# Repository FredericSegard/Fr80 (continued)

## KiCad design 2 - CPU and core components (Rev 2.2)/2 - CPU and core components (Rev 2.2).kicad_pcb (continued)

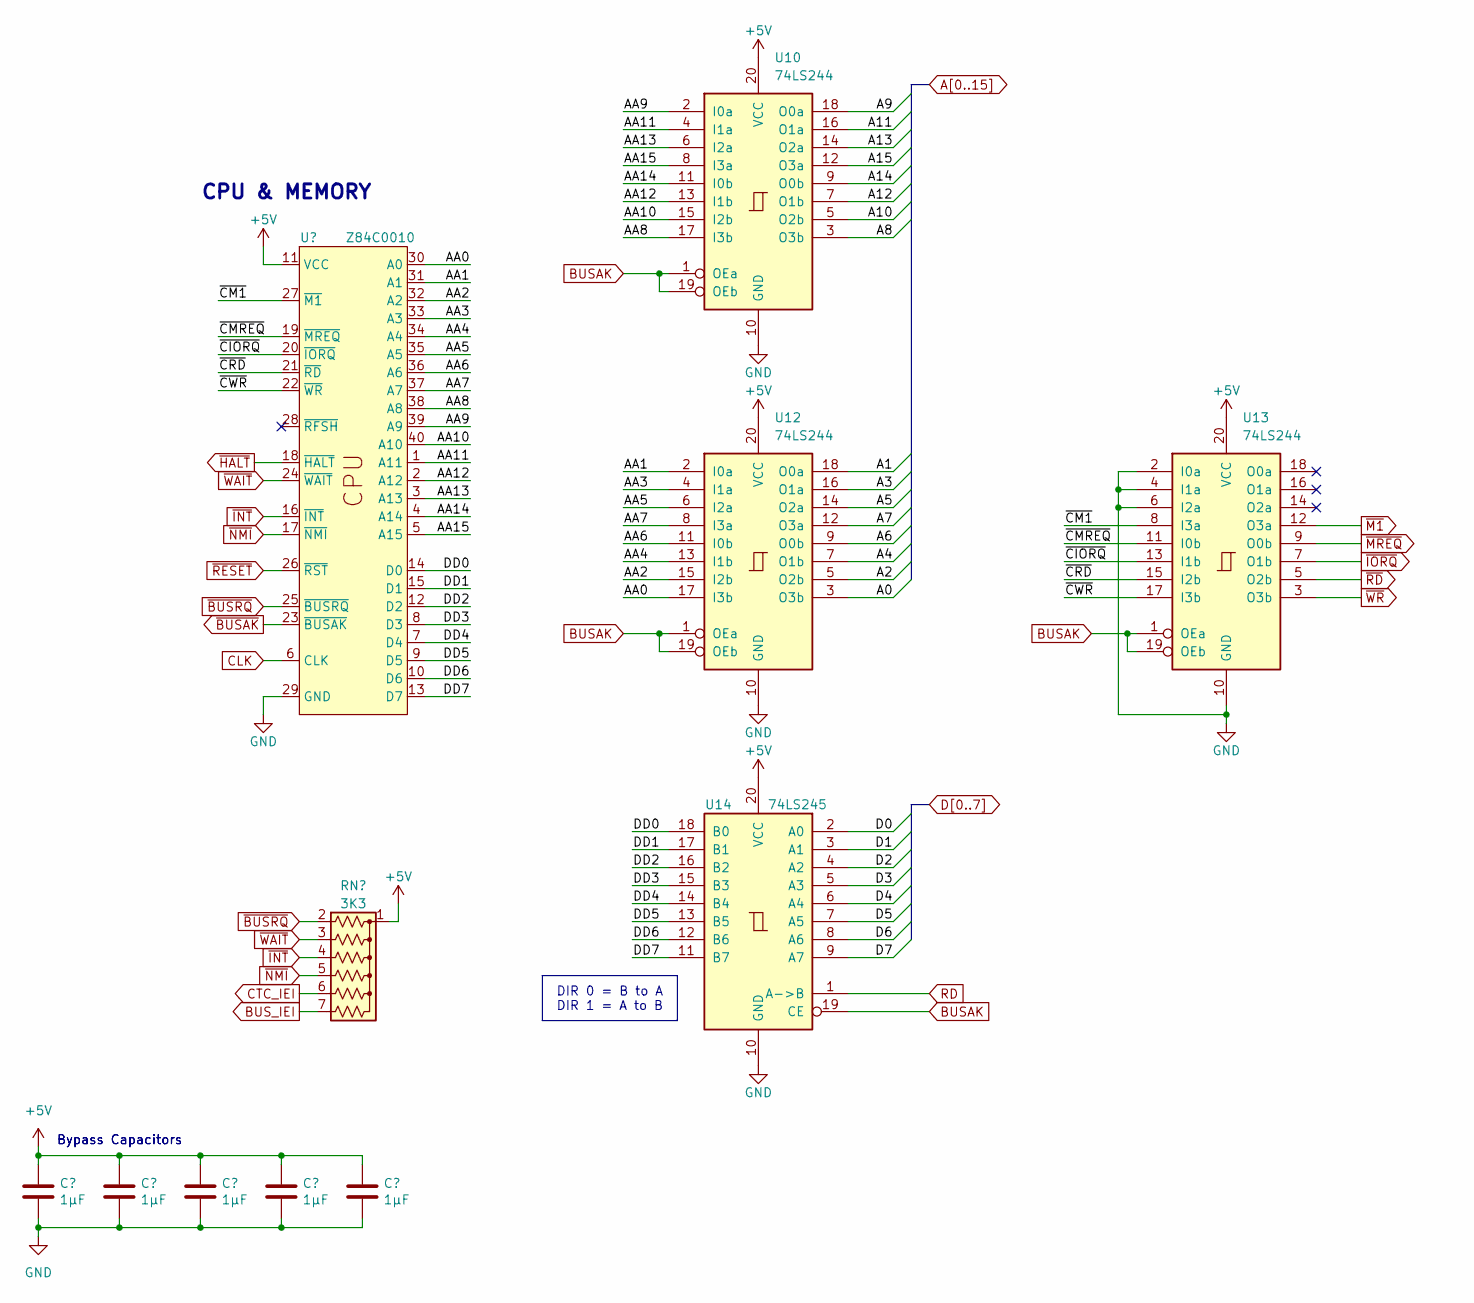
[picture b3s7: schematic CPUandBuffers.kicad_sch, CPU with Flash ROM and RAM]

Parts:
C12, C13, C14, C15, C16: 1µF; C_Disc_D3.4mm_W2.1mm_P2.50mm
RN4: 3K3; R_Array_SIP7
U10, U12, U13: 74LS244; DIP-20_W7.62mm_Socket
U11: Z84C0010; DIP-40_W15.24mm_Socket
U14: 74LS245; DIP-20_W7.62mm_Socket

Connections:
+5V: C12.1, C13.1, C14.1, C15.1, C16.1, RN4.1 (common), U10.20 (VCC), U11.11 (VCC), U12.20 (VCC), U13.20 (VCC), U14.20 (VCC); also elsewhere on the board
/CPU and Buffers/AA0: U11.30 (A0), U12.17 (I3b)
/CPU and Buffers/AA1: U11.31 (A1), U12.2 (I0a)
/CPU and Buffers/AA2: U11.32 (A2), U12.15 (I2b)
/CPU and Buffers/AA3: U11.33 (A3), U12.4 (I1a)
/CPU and Buffers/AA4: U11.34 (A4), U12.13 (I1b)
/CPU and Buffers/AA5: U11.35 (A5), U12.6 (I2a)
/CPU and Buffers/AA6: U11.36 (A6), U12.11 (I0b)
/CPU and Buffers/AA7: U11.37 (A7), U12.8 (I3a)
/CPU and Buffers/AA8: U10.17 (I3b), U11.38 (A8)
/CPU and Buffers/AA9: U10.2 (I0a), U11.39 (A9)
/CPU and Buffers/AA10: U10.15 (I2b), U11.40 (A10)
/CPU and Buffers/AA11: U10.4 (I1a), U11.1 (A11)
/CPU and Buffers/AA12: U10.13 (I1b), U11.2 (A12)
/CPU and Buffers/AA13: U10.6 (I2a), U11.3 (A13)
/CPU and Buffers/AA14: U10.11 (I0b), U11.4 (A14)
/CPU and Buffers/AA15: U10.8 (I3a), U11.5 (A15)
/CPU and Buffers/DD0: U11.14 (D0), U14.18 (B0)
/CPU and Buffers/DD1: U11.15 (D1), U14.17 (B1)
/CPU and Buffers/DD2: U11.12 (D2), U14.16 (B2)
/CPU and Buffers/DD3: U11.8 (D3), U14.15 (B3)
/CPU and Buffers/DD4: U11.7 (D4), U14.14 (B4)
/CPU and Buffers/DD5: U11.9 (D5), U14.13 (B5)
/CPU and Buffers/DD6: U11.10 (D6), U14.12 (B6)
/CPU and Buffers/DD7: U11.13 (D7), U14.11 (B7)
/CPU and Buffers/~CIORQ: U11.20 (~IORQ), U13.13 (I1b)
/CPU and Buffers/~CM1: U11.27 (~M1), U13.8 (I3a)
/CPU and Buffers/~CMREQ: U11.19 (~MREQ), U13.11 (I0b)
/CPU and Buffers/~CRD: U11.21 (~RD), U13.15 (I2b)
/CPU and Buffers/~CWR: U11.22 (~WR), U13.17 (I3b)
A0: U12.3 (O3b); also elsewhere on the board
A1: U12.18 (O0a); also elsewhere on the board
A2: U12.5 (O2b); also elsewhere on the board
A3: U12.16 (O1a); also elsewhere on the board
A4: U12.7 (O1b); also elsewhere on the board
A5: U12.14 (O2a); also elsewhere on the board
A6: U12.9 (O0b); also elsewhere on the board
A7: U12.12 (O3a); also elsewhere on the board
A8: U10.3 (O3b); also elsewhere on the board
A9: U10.18 (O0a); also elsewhere on the board
A10: U10.5 (O2b); also elsewhere on the board
A11: U10.16 (O1a); also elsewhere on the board
A12: U10.7 (O1b); also elsewhere on the board
A13: U10.14 (O2a); also elsewhere on the board
A14: U10.9 (O0b); also elsewhere on the board
A15: U10.12 (O3a); also elsewhere on the board
BUSAK: U10.1 (OEa), U10.19 (OEb), U12.1 (OEa), U12.19 (OEb), U13.1 (OEa), U13.19 (OEb), U14.19 (CE); also elsewhere on the board
BUS_IEI: RN4.7 (R6); also elsewhere on the board
CLK: U11.6 (CLK); also elsewhere on the board
CTC_IEI: RN4.6 (R5); also elsewhere on the board
D0: U14.2 (A0); also elsewhere on the board
D1: U14.3 (A1); also elsewhere on the board
D2: U14.4 (A2); also elsewhere on the board
D3: U14.5 (A3); also elsewhere on the board
D4: U14.6 (A4); also elsewhere on the board
D5: U14.7 (A5); also elsewhere on the board
D6: U14.8 (A6); also elsewhere on the board
D7: U14.9 (A7); also elsewhere on the board
GND: C12.2, C13.2, C14.2, C15.2, C16.2, U10.10 (GND), U11.29 (GND), U12.10 (GND), U13.2 (I0a), U13.4 (I1a), U13.6 (I2a), U13.10 (GND), U14.10 (GND); also elsewhere on the board
RD: U14.1 (A->B); also elsewhere on the board
~BUSAK: U11.23 (~BUSAK); also elsewhere on the board
~BUSRQ: RN4.2 (R1), U11.25 (~BUSRQ); also elsewhere on the board
~HALT: U11.18 (~HALT); also elsewhere on the board
~INT: RN4.4 (R3), U11.16 (~INT); also elsewhere on the board
~IORQ: U13.7 (O1b); also elsewhere on the board
~M1: U13.12 (O3a); also elsewhere on the board
~MREQ: U13.9 (O0b); also elsewhere on the board
~NMI: RN4.5 (R4), U11.17 (~NMI); also elsewhere on the board
~RD: U13.5 (O2b); also elsewhere on the board
~RESET: U11.26 (~RST); also elsewhere on the board
~WAIT: RN4.3 (R2), U11.24 (~WAIT); also elsewhere on the board
~WR: U13.3 (O3b); also elsewhere on the board

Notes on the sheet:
DIR 0 = B to A DIR 1 = A to B
Bypass Capacitors
CPU & MEMORY

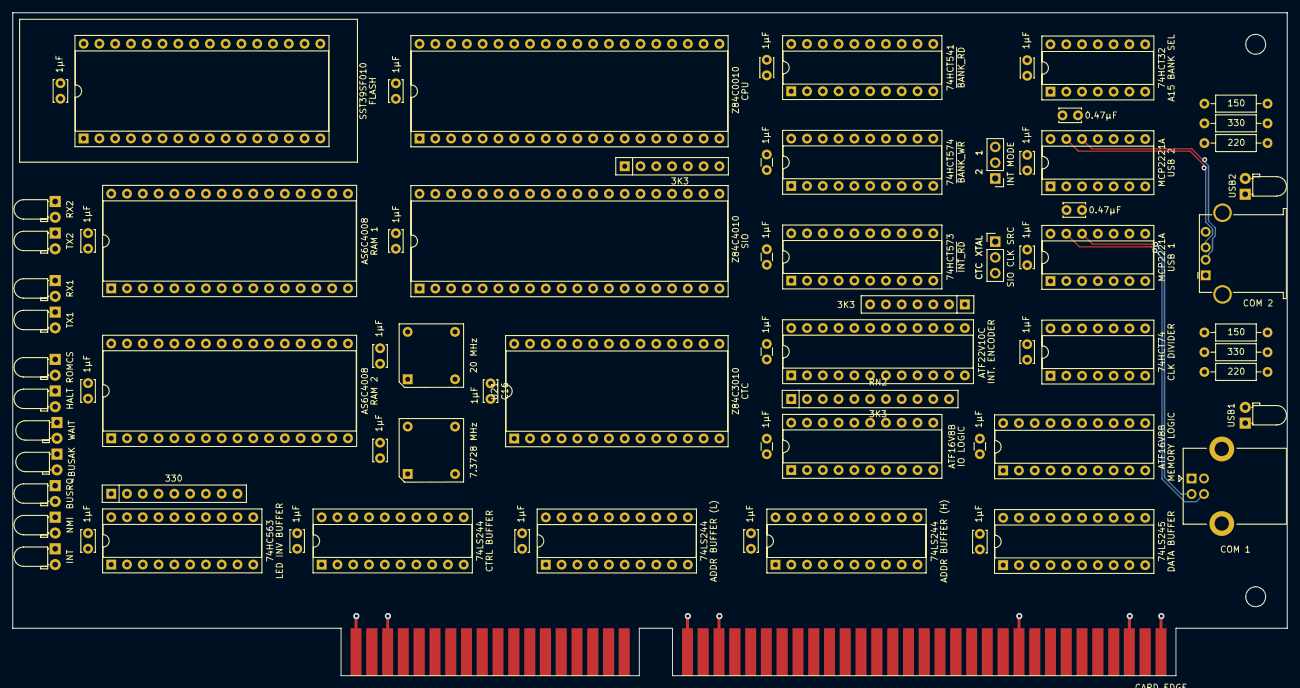
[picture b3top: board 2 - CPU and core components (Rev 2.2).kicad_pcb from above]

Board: 4 copper layers, 205.1 x 106.7 mm, 76 parts (0 on the bottom side), 160 nets.

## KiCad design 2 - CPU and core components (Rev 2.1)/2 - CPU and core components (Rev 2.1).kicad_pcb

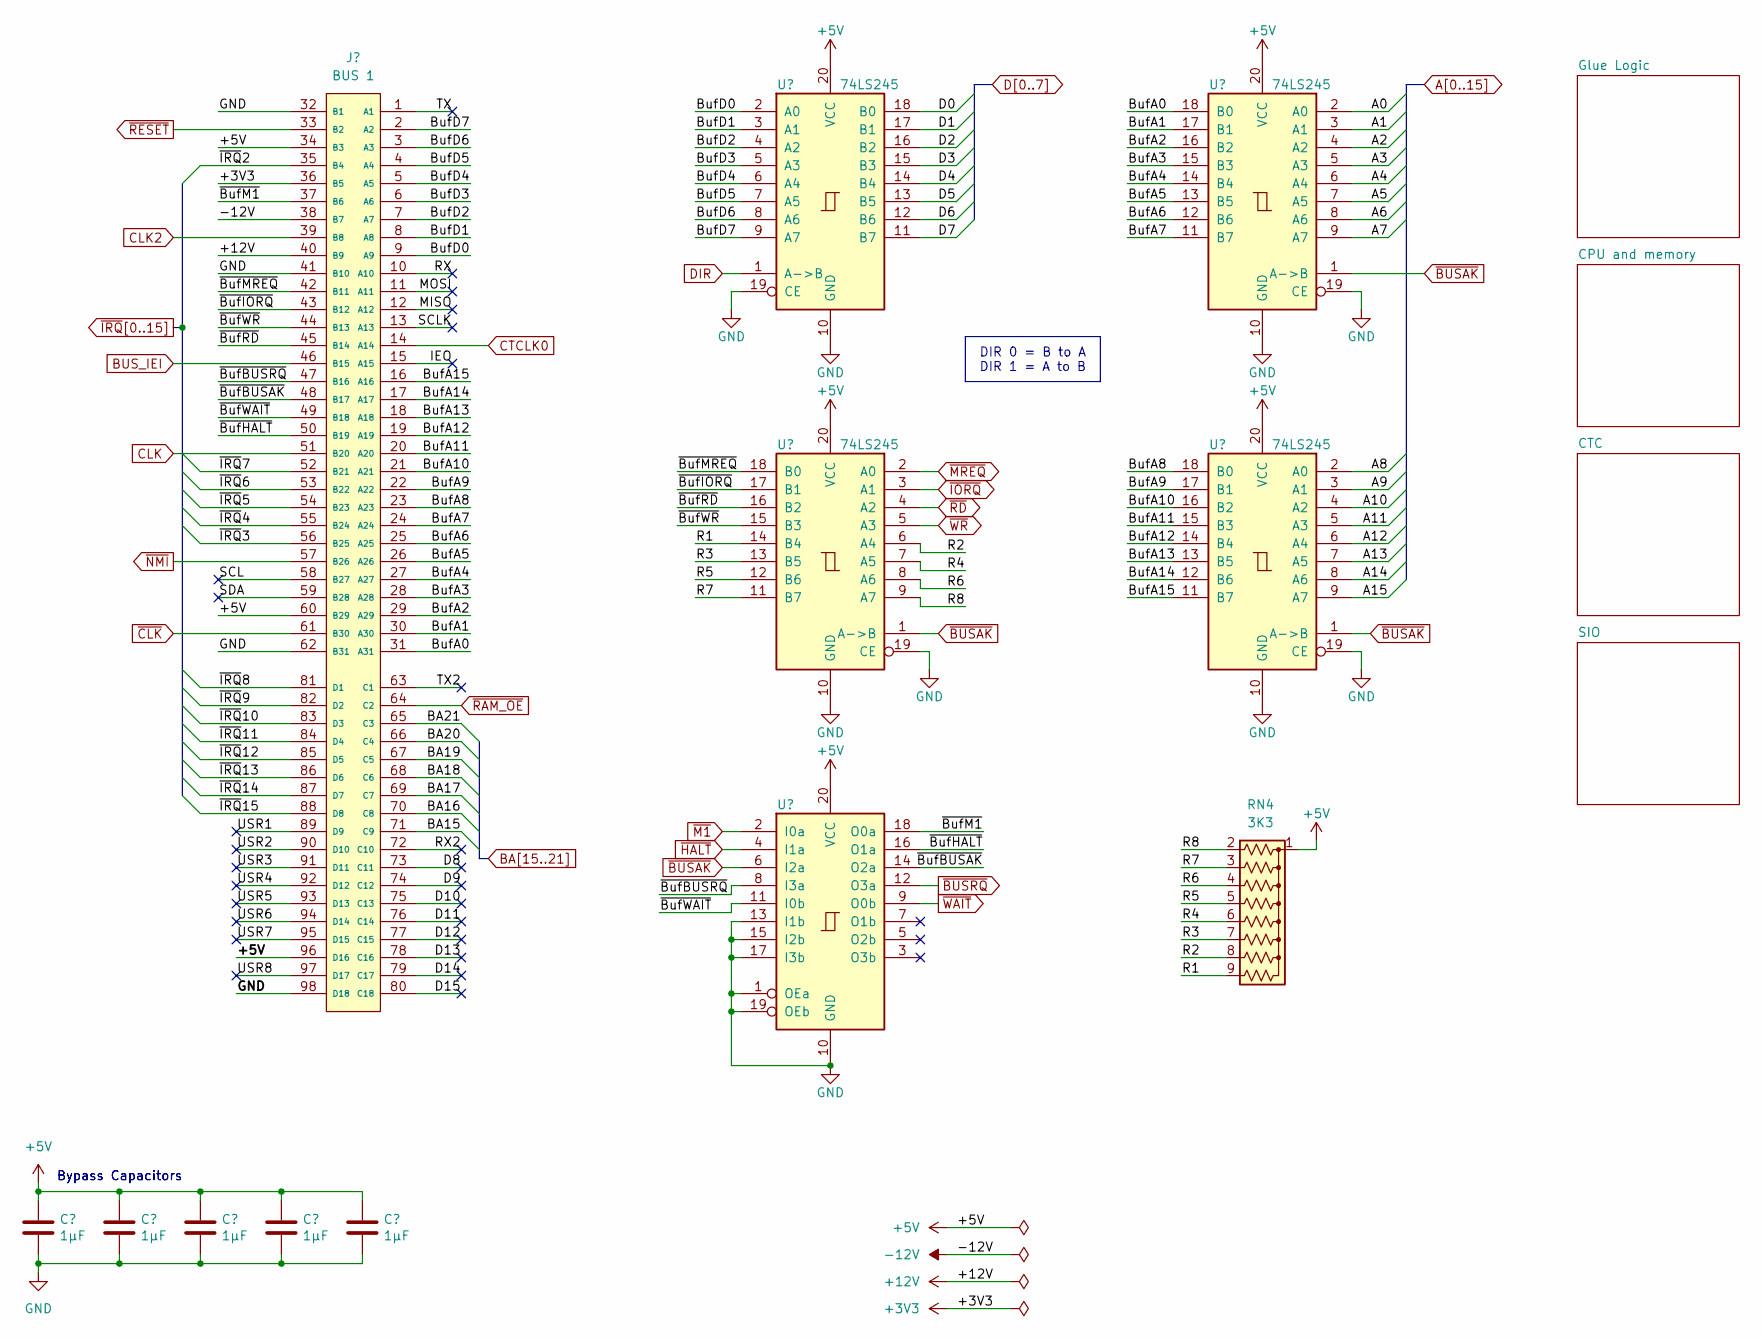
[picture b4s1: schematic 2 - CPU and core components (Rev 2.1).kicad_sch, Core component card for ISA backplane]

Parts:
C1, C2, C3, C4, C5: 1µF; C_Disc_D3.4mm_W2.1mm_P2.50mm
J1: BUS 1; BUS_AT v2
RN4: 3K3; R_Array_SIP9
U1, U2, U4, U5: 74LS245; DIP-20_W7.62mm_Socket
U3: 74LS244; DIP-20_W7.62mm_Socket

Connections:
+3V3: J1.36 (B5)
+12V: J1.40 (B9)
-12V: J1.38 (B7)
/BufA0: J1.31 (A31), U4.18 (B0)
/BufA1: J1.30 (A30), U4.17 (B1)
/BufA2: J1.29 (A29), U4.16 (B2)
/BufA3: J1.28 (A28), U4.15 (B3)
/BufA4: J1.27 (A27), U4.14 (B4)
/BufA5: J1.26 (A26), U4.13 (B5)
/BufA6: J1.25 (A25), U4.12 (B6)
/BufA7: J1.24 (A24), U4.11 (B7)
/BufA8: J1.23 (A23), U5.18 (B0)
/BufA9: J1.22 (A22), U5.17 (B1)
/BufA10: J1.21 (A21), U5.16 (B2)
/BufA11: J1.20 (A20), U5.15 (B3)
/BufA12: J1.19 (A19), U5.14 (B4)
/BufA13: J1.18 (A18), U5.13 (B5)
/BufA14: J1.17 (A17), U5.12 (B6)
/BufA15: J1.16 (A16), U5.11 (B7)
/BufD0: J1.9 (A9), U1.2 (A0)
/BufD1: J1.8 (A8), U1.3 (A1)
/BufD2: J1.7 (A7), U1.4 (A2)
/BufD3: J1.6 (A6), U1.5 (A3)
/BufD4: J1.5 (A5), U1.6 (A4)
/BufD5: J1.4 (A4), U1.7 (A5)
/BufD6: J1.3 (A3), U1.8 (A6)
/BufD7: J1.2 (A2), U1.9 (A7)
/D8: J1.73 (C11)
/D9: J1.74 (C12)
/D10: J1.75 (C13)
/D11: J1.76 (C14)
/D12: J1.77 (C15)
/D13: J1.78 (C16)
/D14: J1.79 (C17)
/D15: J1.80 (C18)
/IEO: J1.15 (A15)
/MISO: J1.12 (A12)
/MOSI: J1.11 (A11)
/R1: RN4.9 (R8), U2.14 (B4)
/R2: RN4.8 (R7), U2.6 (A4)
/R3: RN4.7 (R6), U2.13 (B5)
/R4: RN4.6 (R5), U2.7 (A5)
/R5: RN4.5 (R4), U2.12 (B6)
/R6: RN4.4 (R3), U2.8 (A6)
/R7: RN4.3 (R2), U2.11 (B7)
/R8: RN4.2 (R1), U2.9 (A7)
/RX: J1.10 (A10)
/RX2: J1.72 (C10)
/SCL: J1.58 (B27)
/SCLK: J1.13 (A13)
/SDA: J1.59 (B28)
/TX: J1.1 (A1)
/TX2: J1.63 (C1)
/USR1: J1.89 (D9)
/USR2: J1.90 (D10)
/USR3: J1.91 (D11)
/USR4: J1.92 (D12)
/USR5: J1.93 (D13)
/USR6: J1.94 (D14)
/USR7: J1.95 (D15)
/USR8: J1.97 (D17)
/~BufBUSAK: J1.48 (B17), U3.14 (O2a)
/~BufBUSRQ: J1.47 (B16), U3.8 (I3a)
/~BufHALT: J1.50 (B19), U3.16 (O1a)
/~BufIORQ: J1.43 (B12), U2.17 (B1)
/~BufM1: J1.37 (B6), U3.18 (O0a)
/~BufMREQ: J1.42 (B11), U2.18 (B0)
/~BufRD: J1.45 (B14), U2.16 (B2)
/~BufWAIT: J1.49 (B18), U3.11 (I0b)
/~BufWR: J1.44 (B13), U2.15 (B3)
A0: U4.2 (A0); also elsewhere on the board
A1: U4.3 (A1); also elsewhere on the board
A2: U4.4 (A2); also elsewhere on the board
A3: U4.5 (A3); also elsewhere on the board
A4: U4.6 (A4); also elsewhere on the board
A5: U4.7 (A5); also elsewhere on the board
A6: U4.8 (A6); also elsewhere on the board
A7: U4.9 (A7); also elsewhere on the board
A8: U5.2 (A0); also elsewhere on the board
A9: U5.3 (A1); also elsewhere on the board
A10: U5.4 (A2); also elsewhere on the board
A11: U5.5 (A3); also elsewhere on the board
A12: U5.6 (A4); also elsewhere on the board
A13: U5.7 (A5); also elsewhere on the board
A14: U5.8 (A6); also elsewhere on the board
A15: U5.9 (A7); also elsewhere on the board
BA15: J1.71 (C9); also elsewhere on the board
BA16: J1.70 (C8); also elsewhere on the board
BA17: J1.69 (C7); also elsewhere on the board
BA18: J1.68 (C6); also elsewhere on the board
BA19: J1.67 (C5); also elsewhere on the board
BA20: J1.66 (C4); also elsewhere on the board
BA21: J1.65 (C3); also elsewhere on the board
BUS_IEI: J1.46 (B15); also elsewhere on the board
CLK: J1.51 (B20); also elsewhere on the board
CLK2: J1.39 (B8); also elsewhere on the board
CTCLK0: J1.14 (A14); also elsewhere on the board
D0: U1.18 (B0); also elsewhere on the board
D1: U1.17 (B1); also elsewhere on the board
D2: U1.16 (B2); also elsewhere on the board
D3: U1.15 (B3); also elsewhere on the board
D4: U1.14 (B4); also elsewhere on the board
D5: U1.13 (B5); also elsewhere on the board
D6: U1.12 (B6); also elsewhere on the board
D7: U1.11 (B7); also elsewhere on the board
DIR: U1.1 (A->B); also elsewhere on the board
~BUSAK: U2.1 (A->B), U3.6 (I2a), U4.1 (A->B), U5.1 (A->B); also elsewhere on the board
~BUSRQ: U3.12 (O3a); also elsewhere on the board
~CLK: J1.61 (B30); also elsewhere on the board
~HALT: U3.4 (I1a); also elsewhere on the board
~IORQ: U2.3 (A1); also elsewhere on the board
~IRQ2: J1.35 (B4); also elsewhere on the board
~IRQ3: J1.56 (B25); also elsewhere on the board
~IRQ4: J1.55 (B24); also elsewhere on the board
~IRQ5: J1.54 (B23); also elsewhere on the board
~IRQ6: J1.53 (B22); also elsewhere on the board
~IRQ7: J1.52 (B21); also elsewhere on the board
~IRQ8: J1.81 (D1); also elsewhere on the board
~IRQ9: J1.82 (D2); also elsewhere on the board
~IRQ10: J1.83 (D3); also elsewhere on the board
~IRQ11: J1.84 (D4); also elsewhere on the board
~IRQ12: J1.85 (D5); also elsewhere on the board
~IRQ13: J1.86 (D6); also elsewhere on the board
~IRQ14: J1.87 (D7); also elsewhere on the board
~IRQ15: J1.88 (D8); also elsewhere on the board
~M1: U3.2 (I0a); also elsewhere on the board
~MREQ: U2.2 (A0); also elsewhere on the board
~NMI: J1.57 (B26); also elsewhere on the board
~RAM_OE: J1.64 (C2); also elsewhere on the board
~RD: U2.4 (A2); also elsewhere on the board
~RESET: J1.33 (B2); also elsewhere on the board
~WAIT: U3.9 (O0b); also elsewhere on the board
~WR: U2.5 (A3); also elsewhere on the board

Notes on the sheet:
DIR 0 = B to A DIR 1 = A to B
Bypass Capacitors

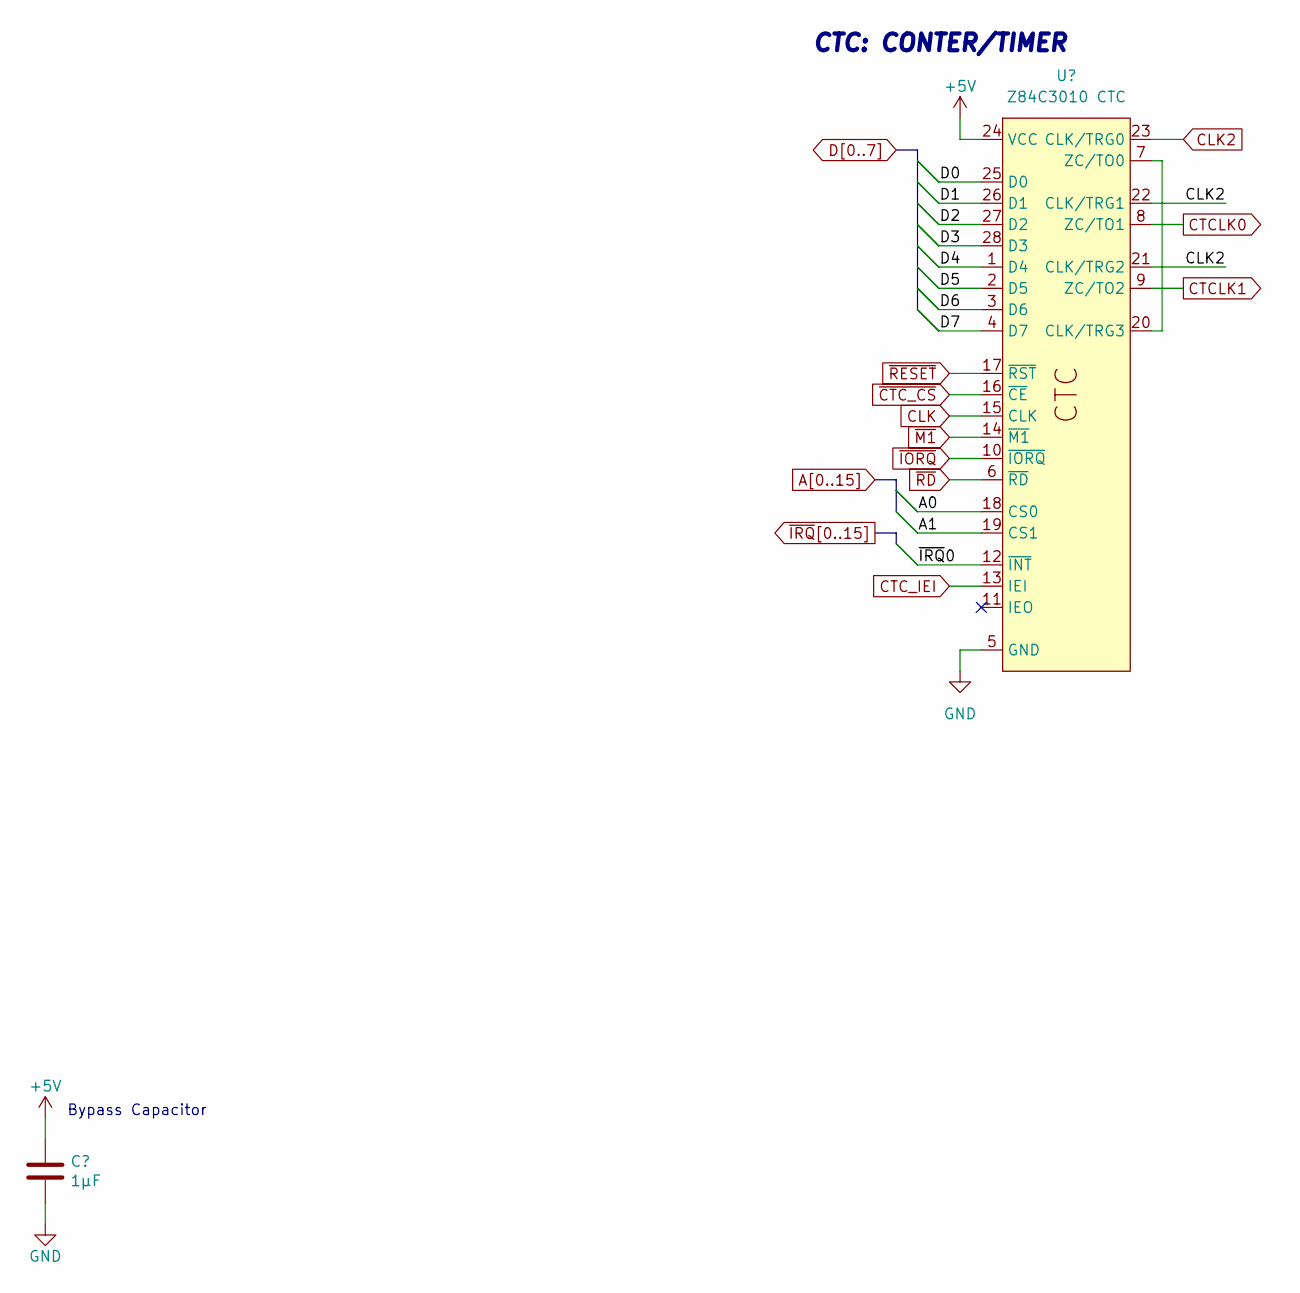
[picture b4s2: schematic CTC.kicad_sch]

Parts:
C20: 1µF; C_Disc_D3.4mm_W2.1mm_P2.50mm
U18: Z84C3010 CTC; DIP-28_W15.24mm_Socket

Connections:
A0: U18.18 (CS0); also elsewhere on the board
A1: U18.19 (CS1); also elsewhere on the board
CLK: U18.15 (CLK); also elsewhere on the board
CLK2: U18.21 (CLK/TRG2), U18.22 (CLK/TRG1), U18.23 (CLK/TRG0); also elsewhere on the board
CTCLK0: U18.8 (ZC/TO1); also elsewhere on the board
CTCLK1: U18.9 (ZC/TO2); also elsewhere on the board
CTC_IEI: U18.13 (IEI); also elsewhere on the board
D0: U18.25 (D0); also elsewhere on the board
D1: U18.26 (D1); also elsewhere on the board
D2: U18.27 (D2); also elsewhere on the board
D3: U18.28 (D3); also elsewhere on the board
D4: U18.1 (D4); also elsewhere on the board
D5: U18.2 (D5); also elsewhere on the board
D6: U18.3 (D6); also elsewhere on the board
D7: U18.4 (D7); also elsewhere on the board
unnamed: U18.7 (ZC/TO0), U18.20 (CLK/TRG3)
~CTC_CS: U18.16 (~CE); also elsewhere on the board
~IORQ: U18.10 (~IORQ); also elsewhere on the board
~IRQ0: U18.12 (~INT); also elsewhere on the board
~M1: U18.14 (~M1); also elsewhere on the board
~RD: U18.6 (~RD); also elsewhere on the board
~RESET: U18.17 (~RST); also elsewhere on the board

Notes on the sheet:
CTC: CONTER/TIMER
Bypass Capacitor

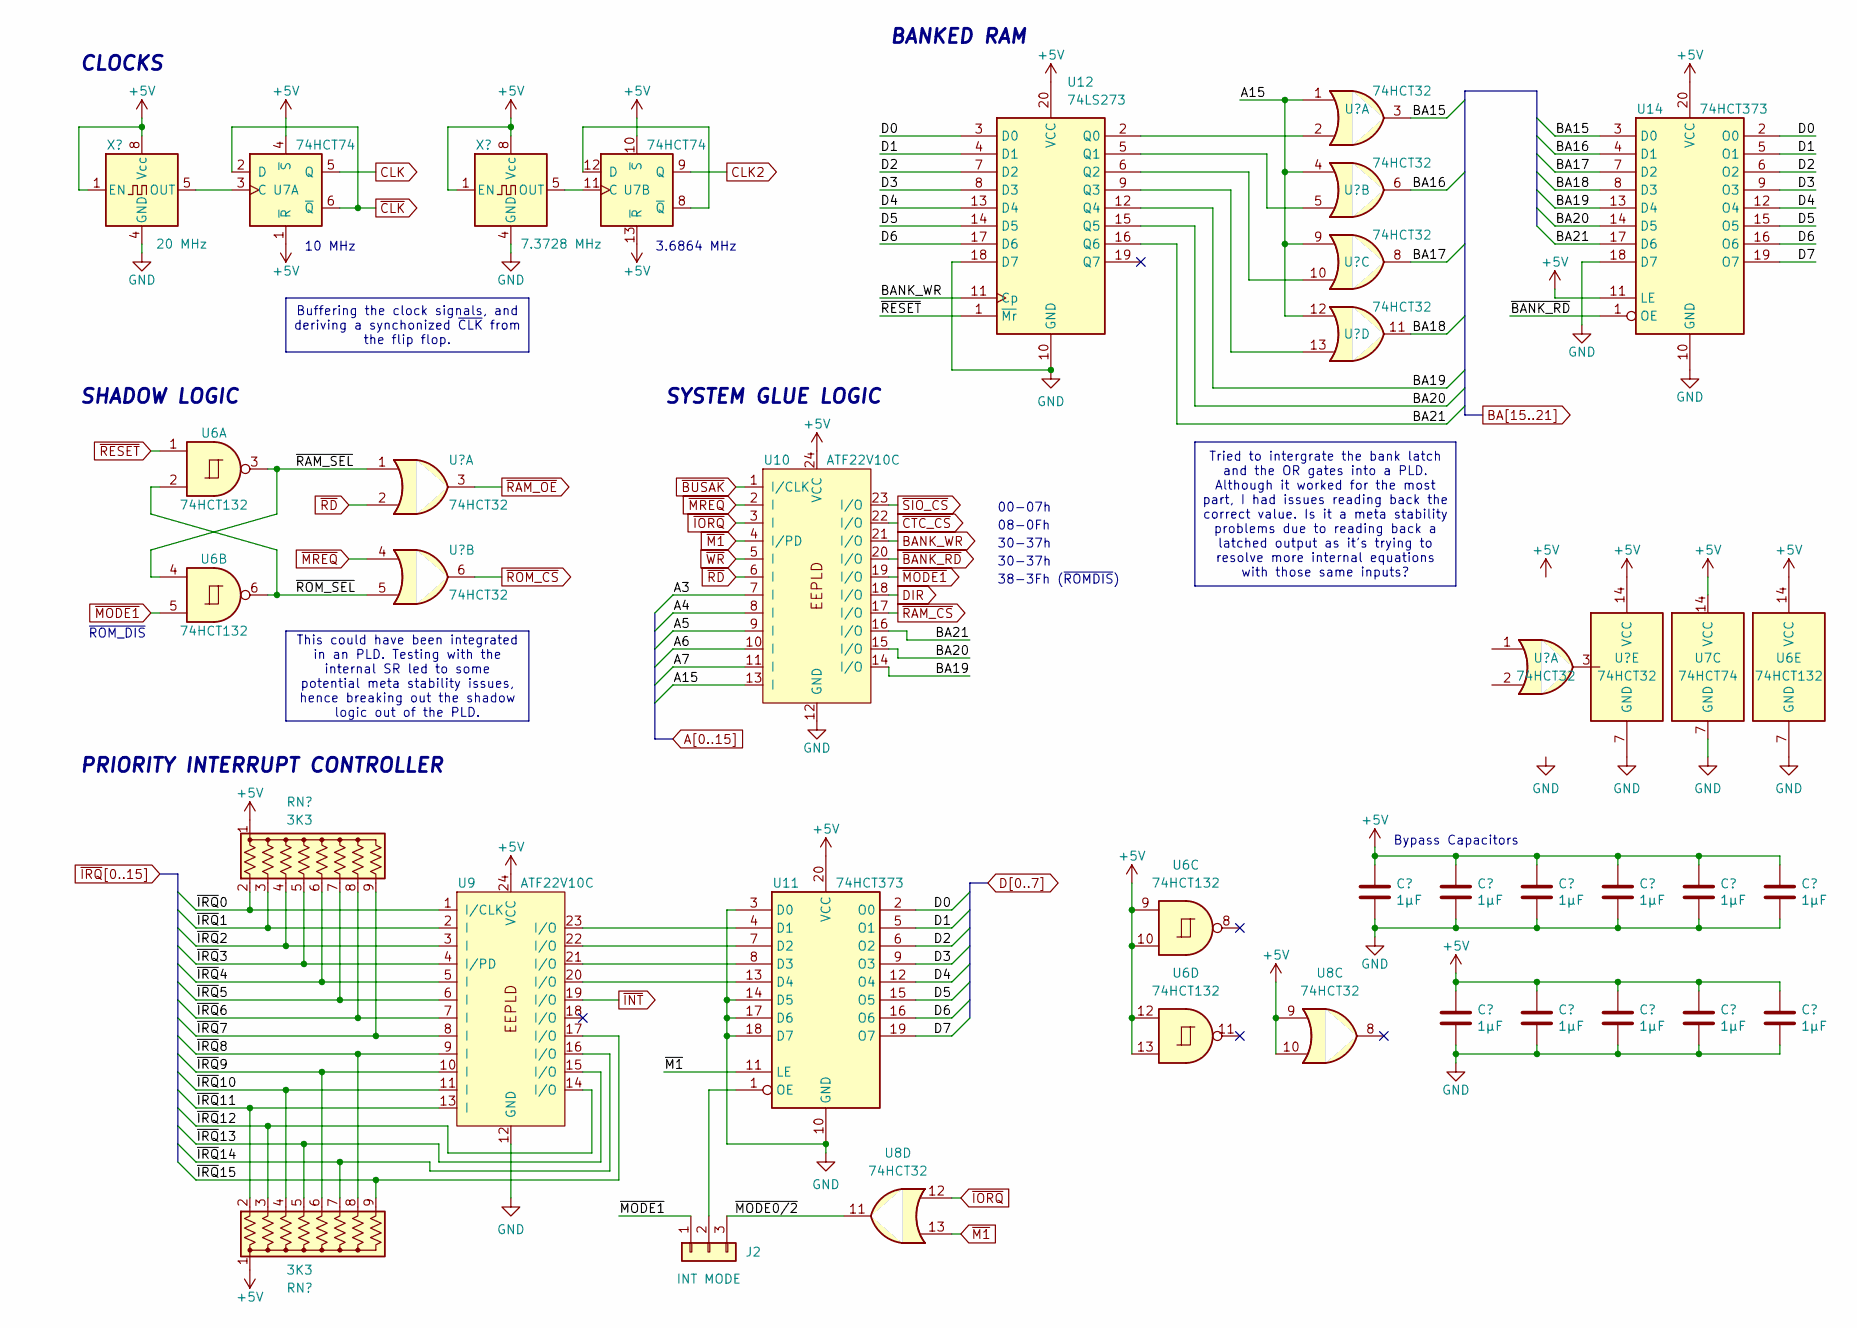
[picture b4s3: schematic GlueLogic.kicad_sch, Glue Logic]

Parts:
C6, C7, C8, C9, C12: 1µF; C_Disc_D3.0mm_W1.6mm_P2.50mm
C10, C11, C13, C14, C15, C16: 1µF; C_Disc_D3.0mm_W2.0mm_P2.50mm
J2: INT MODE; PinHeader_1x03_P2.54mm_Vertical
RN1, RN2: 3K3; R_Array_SIP9
U6: 74HCT132; DIP-14_W7.62mm_Socket
U7: 74HCT74; DIP-14_W7.62mm_Socket
U8, U13: 74HCT32; DIP-14_W7.62mm_Socket
U9, U10: ATF22V10C; DIP-24_W7.62mm_Socket
U11, U14: 74HCT373; DIP-20_W7.62mm_Socket
U12: 74LS273; DIP-20_W7.62mm_Socket
X1: 20 MHz; DIP-8-4_W7.62mm_Oscillator_Socket
X2: 7.3728 MHz; DIP-8-4_W7.62mm_Oscillator_Socket

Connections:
/Glue Logic/~MODE0/2: J2.3, U8.11
/Glue Logic/~RAM_SEL: U6.3, U6.4, U8.1
/Glue Logic/~ROM_SEL: U6.2, U6.6, U8.5
A3: U10.7 (I); also elsewhere on the board
A4: U10.8 (I); also elsewhere on the board
A5: U10.9 (I); also elsewhere on the board
A6: U10.10 (I); also elsewhere on the board
A7: U10.11 (I); also elsewhere on the board
A15: U10.13 (I), U13.1, U13.4, U13.9, U13.12; also elsewhere on the board
BA15: U13.3, U14.3 (D0); also elsewhere on the board
BA16: U13.6, U14.4 (D1); also elsewhere on the board
BA17: U13.8, U14.7 (D2); also elsewhere on the board
BA18: U13.11, U14.8 (D3); also elsewhere on the board
BA19: U10.14 (I/O), U12.12 (Q4), U14.13 (D4); also elsewhere on the board
BA20: U10.15 (I/O), U12.15 (Q5), U14.14 (D5); also elsewhere on the board
BA21: U10.16 (I/O), U12.16 (Q6), U14.17 (D6); also elsewhere on the board
BANK_WR: U10.21 (I/O), U12.11 (Cp)
CLK: U7.5 (Q); also elsewhere on the board
CLK2: U7.9 (Q); also elsewhere on the board
D0: U11.2 (O0), U12.3 (D0), U14.2 (O0); also elsewhere on the board
D1: U11.5 (O1), U12.4 (D1), U14.5 (O1); also elsewhere on the board
D2: U11.6 (O2), U12.7 (D2), U14.6 (O2); also elsewhere on the board
D3: U11.9 (O3), U12.8 (D3), U14.9 (O3); also elsewhere on the board
D4: U11.12 (O4), U12.13 (D4), U14.12 (O4); also elsewhere on the board
D5: U11.15 (O5), U12.14 (D5), U14.15 (O5); also elsewhere on the board
D6: U11.16 (O6), U12.17 (D6), U14.16 (O6); also elsewhere on the board
D7: U11.19 (O7), U14.19 (O7); also elsewhere on the board
DIR: U10.18 (I/O); also elsewhere on the board
unnamed: J2.2, U11.1 (OE)
unnamed: U7.3 (C), X1.5 (OUT)
unnamed: U7.11 (C), X2.5 (OUT)
unnamed: U7.8 (~Q), U7.12 (D)
unnamed: U9.23 (I/O), U11.4 (D1)
unnamed: U9.22 (I/O), U11.7 (D2)
unnamed: U9.21 (I/O), U11.8 (D3)
unnamed: U9.20 (I/O), U11.13 (D4)
unnamed: U12.2 (Q0), U13.2
unnamed: U12.5 (Q1), U13.5
unnamed: U12.6 (Q2), U13.10
unnamed: U12.9 (Q3), U13.13
~BANK_RD: U10.20 (I/O), U14.1 (OE)
~BUSAK: U10.1 (I/CLK); also elsewhere on the board
~CLK: U7.2 (D), U7.6 (~Q); also elsewhere on the board
~CTC_CS: U10.22 (I/O); also elsewhere on the board
~INT: U9.19 (I/O); also elsewhere on the board
~IORQ: U8.12, U10.3 (I); also elsewhere on the board
~IRQ0: RN1.2 (R1), U9.1 (I/CLK); also elsewhere on the board
~IRQ1: RN1.3 (R2), U9.2 (I); also elsewhere on the board
~IRQ2: RN1.4 (R3), U9.3 (I); also elsewhere on the board
~IRQ3: RN1.5 (R4), U9.4 (I/PD); also elsewhere on the board
~IRQ4: RN1.6 (R5), U9.5 (I); also elsewhere on the board
~IRQ5: RN1.7 (R6), U9.6 (I); also elsewhere on the board
~IRQ6: RN1.8 (R7), U9.7 (I); also elsewhere on the board
~IRQ7: RN1.9 (R8), U9.8 (I); also elsewhere on the board
~IRQ8: RN2.8 (R7), U9.9 (I); also elsewhere on the board
~IRQ9: RN2.6 (R5), U9.10 (I); also elsewhere on the board
~IRQ10: RN2.4 (R3), U9.11 (I); also elsewhere on the board
~IRQ11: RN2.2 (R1), U9.13 (I); also elsewhere on the board
~IRQ12: RN2.3 (R2), U9.14 (I/O); also elsewhere on the board
~IRQ13: RN2.5 (R4), U9.15 (I/O); also elsewhere on the board
~IRQ14: RN2.7 (R6), U9.16 (I/O); also elsewhere on the board
~IRQ15: RN2.9 (R8), U9.17 (I/O); also elsewhere on the board
~M1: U8.13, U10.4 (I/PD), U11.11 (LE); also elsewhere on the board
~MODE1: J2.1, U6.5, U10.19 (I/O)
~MREQ: U8.4, U10.2 (I); also elsewhere on the board
~RAM_CS: U10.17 (I/O); also elsewhere on the board
~RAM_OE: U8.3; also elsewhere on the board
~RD: U8.2, U10.6 (I); also elsewhere on the board
~RESET: U6.1, U12.1 (~Mr); also elsewhere on the board
~ROM_CS: U8.6; also elsewhere on the board
~SIO_CS: U10.23 (I/O); also elsewhere on the board
~WR: U10.5 (I); also elsewhere on the board

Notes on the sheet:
Buffering the clock signals, and deriving a synchonized ~{CLK} from the flip flop.
Tried to intergrate the bank latch and the OR gates into a PLD. Although it worked for the most part, I had issues reading back the correct value. Is it a meta stability problems due to reading back a latched output as it's trying to resolve more internal equations with those same inputs?
This could have been integrated in an PLD. Testing with the internal SR led to some potential meta stability issues, hence breaking out the shadow logic out of the PLD.
Bypass Capacitors
38-3Fh (~{ROMDIS})
08-0Fh
30-37h
BANKED RAM
~{ROM_DIS}
10 MHz
00-07h
PRIORITY INTERRUPT CONTROLLER
CLOCKS
3.6864 MHz
SHADOW LOGIC
SYSTEM GLUE LOGIC

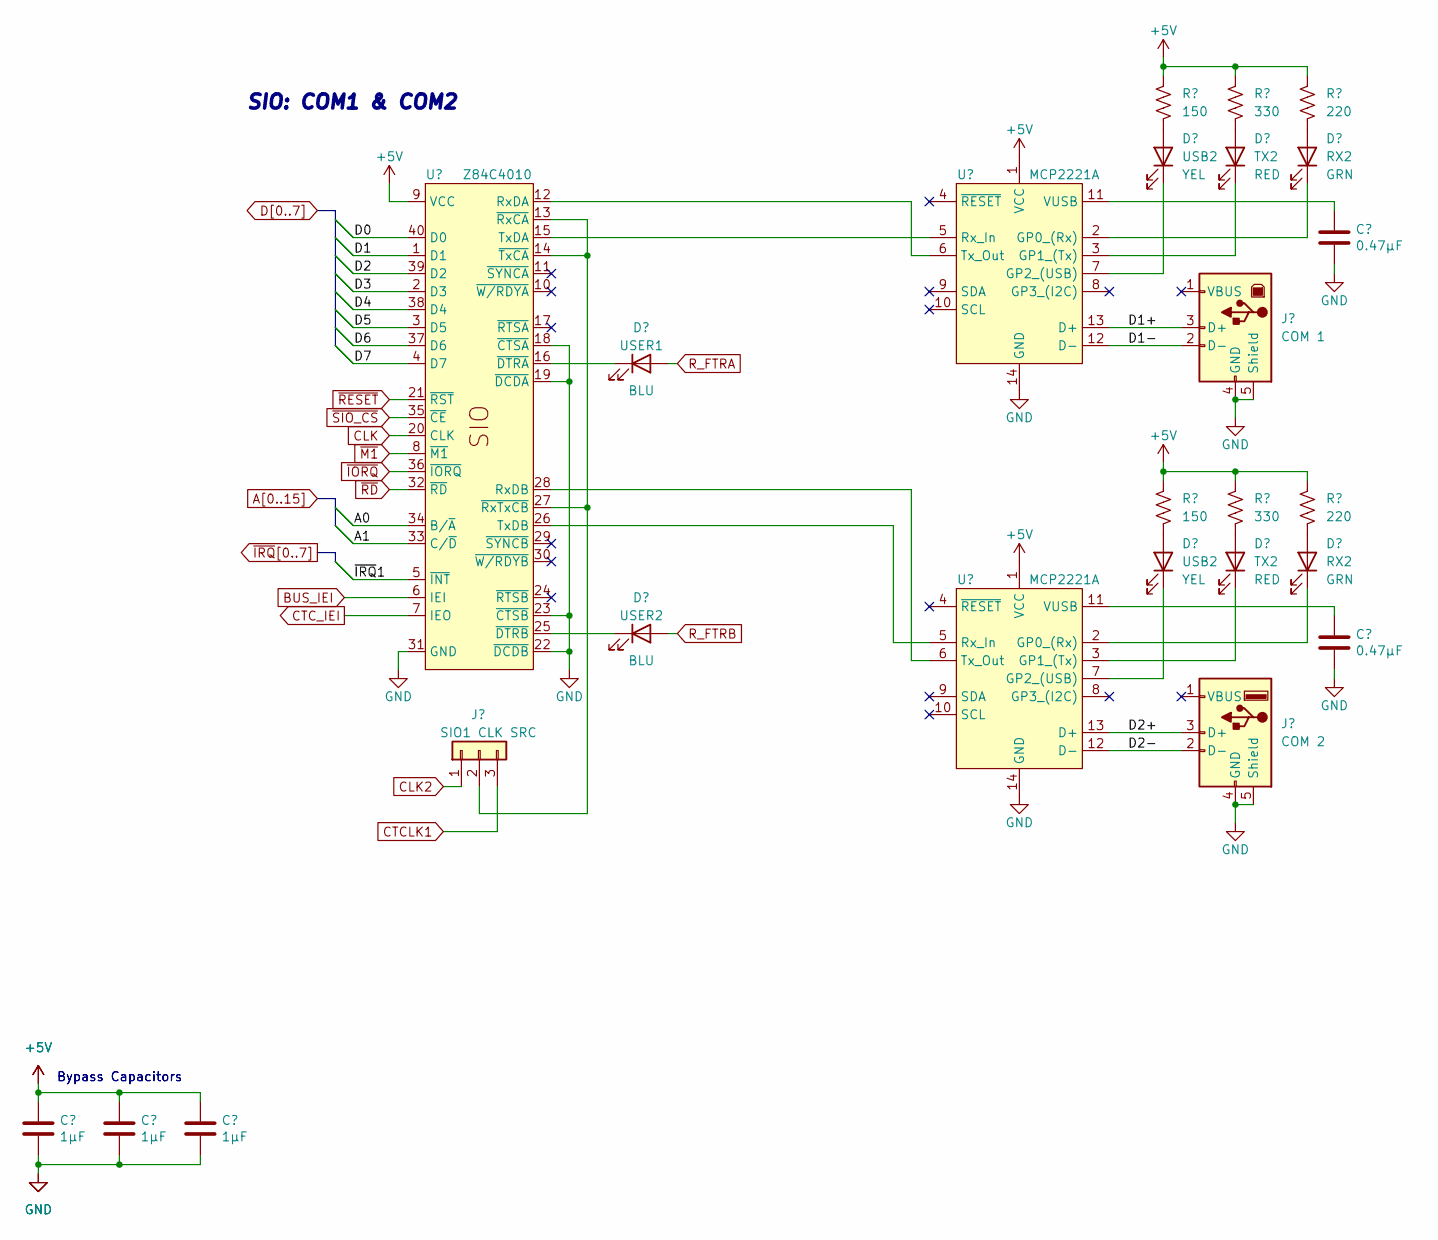
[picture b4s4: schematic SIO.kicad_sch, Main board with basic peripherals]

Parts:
C21, C22, C23: 1µF; C_Disc_D3.4mm_W2.1mm_P2.50mm
C24, C25: 0.47µF; C_Disc_D3.4mm_W2.1mm_P2.50mm
D1: USER1; LED_D3.0mm_Horizontal_O1.27mm_Z2.0mm_Clear
D2: USER2; LED_D3.0mm_Horizontal_O1.27mm_Z2.0mm_Clear
D3, D4: USB2; LED_D3.0mm_Horizontal_O1.27mm_Z2.0mm_Clear
D5, D6: TX2; LED_D3.0mm_Horizontal_O1.27mm_Z2.0mm_Clear
D7, D8: RX2; LED_D3.0mm_Horizontal_O1.27mm_Z2.0mm_Clear
J3: SIO1 CLK SRC; PinHeader_1x03_P2.54mm_Vertical
J4: COM 1; USB_B_Lumberg_2411_02_Horizontal
J5: COM 2; USB_A_Stewart_SS-52100-001_Horizontal
R1, R2: 150; R_Axial_DIN0207_L6.3mm_D2.5mm_P10.16mm_Horizontal
R3, R4: 330; R_Axial_DIN0207_L6.3mm_D2.5mm_P10.16mm_Horizontal
R5, R6: 220; R_Axial_DIN0207_L6.3mm_D2.5mm_P10.16mm_Horizontal
U19: Z84C4010; DIP-40_W15.24mm_Socket
U20, U21: MCP2221A; DIP-14_W7.62mm_Socket

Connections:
/SIO/D1+: J4.3 (D+), U20.13 (D+)
/SIO/D1-: J4.2 (D-), U20.12 (D-)
/SIO/D2+: J5.3 (D+), U21.13 (D+)
/SIO/D2-: J5.2 (D-), U21.12 (D-)
A0: U19.34 (B/~A); also elsewhere on the board
A1: U19.33 (C/~D); also elsewhere on the board
BUS_IEI: U19.6 (IEI); also elsewhere on the board
CLK: U19.20 (CLK); also elsewhere on the board
CLK2: J3.1; also elsewhere on the board
CTCLK1: J3.3; also elsewhere on the board
CTC_IEI: U19.7 (IEO); also elsewhere on the board
D0: U19.40 (D0); also elsewhere on the board
D1: U19.1 (D1); also elsewhere on the board
D2: U19.39 (D2); also elsewhere on the board
D3: U19.2 (D3); also elsewhere on the board
D4: U19.38 (D4); also elsewhere on the board
D5: U19.3 (D5); also elsewhere on the board
D6: U19.37 (D6); also elsewhere on the board
D7: U19.4 (D7); also elsewhere on the board
unnamed: D2.1 (K), U19.25 (~DTRB)
unnamed: D3.2 (A), R1.1
unnamed: D3.1 (K), U20.7 (GP2_(USB))
unnamed: D4.1 (K), U21.7 (GP2_(USB))
unnamed: D5.2 (A), R3.1
unnamed: D5.1 (K), U20.3 (GP1_(Tx))
unnamed: D6.2 (A), R4.1
unnamed: D6.1 (K), U21.3 (GP1_(Tx))
unnamed: D7.2 (A), R5.1
unnamed: D7.1 (K), U20.2 (GP0_(Rx))
unnamed: D8.2 (A), R6.1
unnamed: D8.1 (K), U21.2 (GP0_(Rx))
unnamed: J3.2, U19.13 (~RxCA), U19.14 (~TxCA), U19.27 (~RxTxCB)
unnamed: U19.12 (RxDA), U20.6 (Tx_Out)
unnamed: U19.28 (RxDB), U21.6 (Tx_Out)
unnamed: U19.15 (TxDA), U20.5 (Rx_In)
unnamed: U19.26 (TxDB), U21.5 (Rx_In)
unnamed: C24.1, U20.11 (VUSB)
unnamed: C25.1, U21.11 (VUSB)
R_FTRB: D2.2 (A); also elsewhere on the board
~IORQ: U19.36 (~IORQ); also elsewhere on the board
~IRQ1: U19.5 (~INT); also elsewhere on the board
~M1: U19.8 (~M1); also elsewhere on the board
~RD: U19.32 (~RD); also elsewhere on the board
~RESET: U19.21 (~RST); also elsewhere on the board
~SIO_CS: U19.35 (~CE); also elsewhere on the board

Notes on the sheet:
SIO: COM1 & COM2
Bypass Capacitors
